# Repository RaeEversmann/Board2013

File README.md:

Board2013
=========

Uses the TI Evaluation boards and breaks out pins plus motor controllers and power regulator to use on various robotic projects. Uses Motor Controller TLE 5205-2G and Buck Regulator LM25765.

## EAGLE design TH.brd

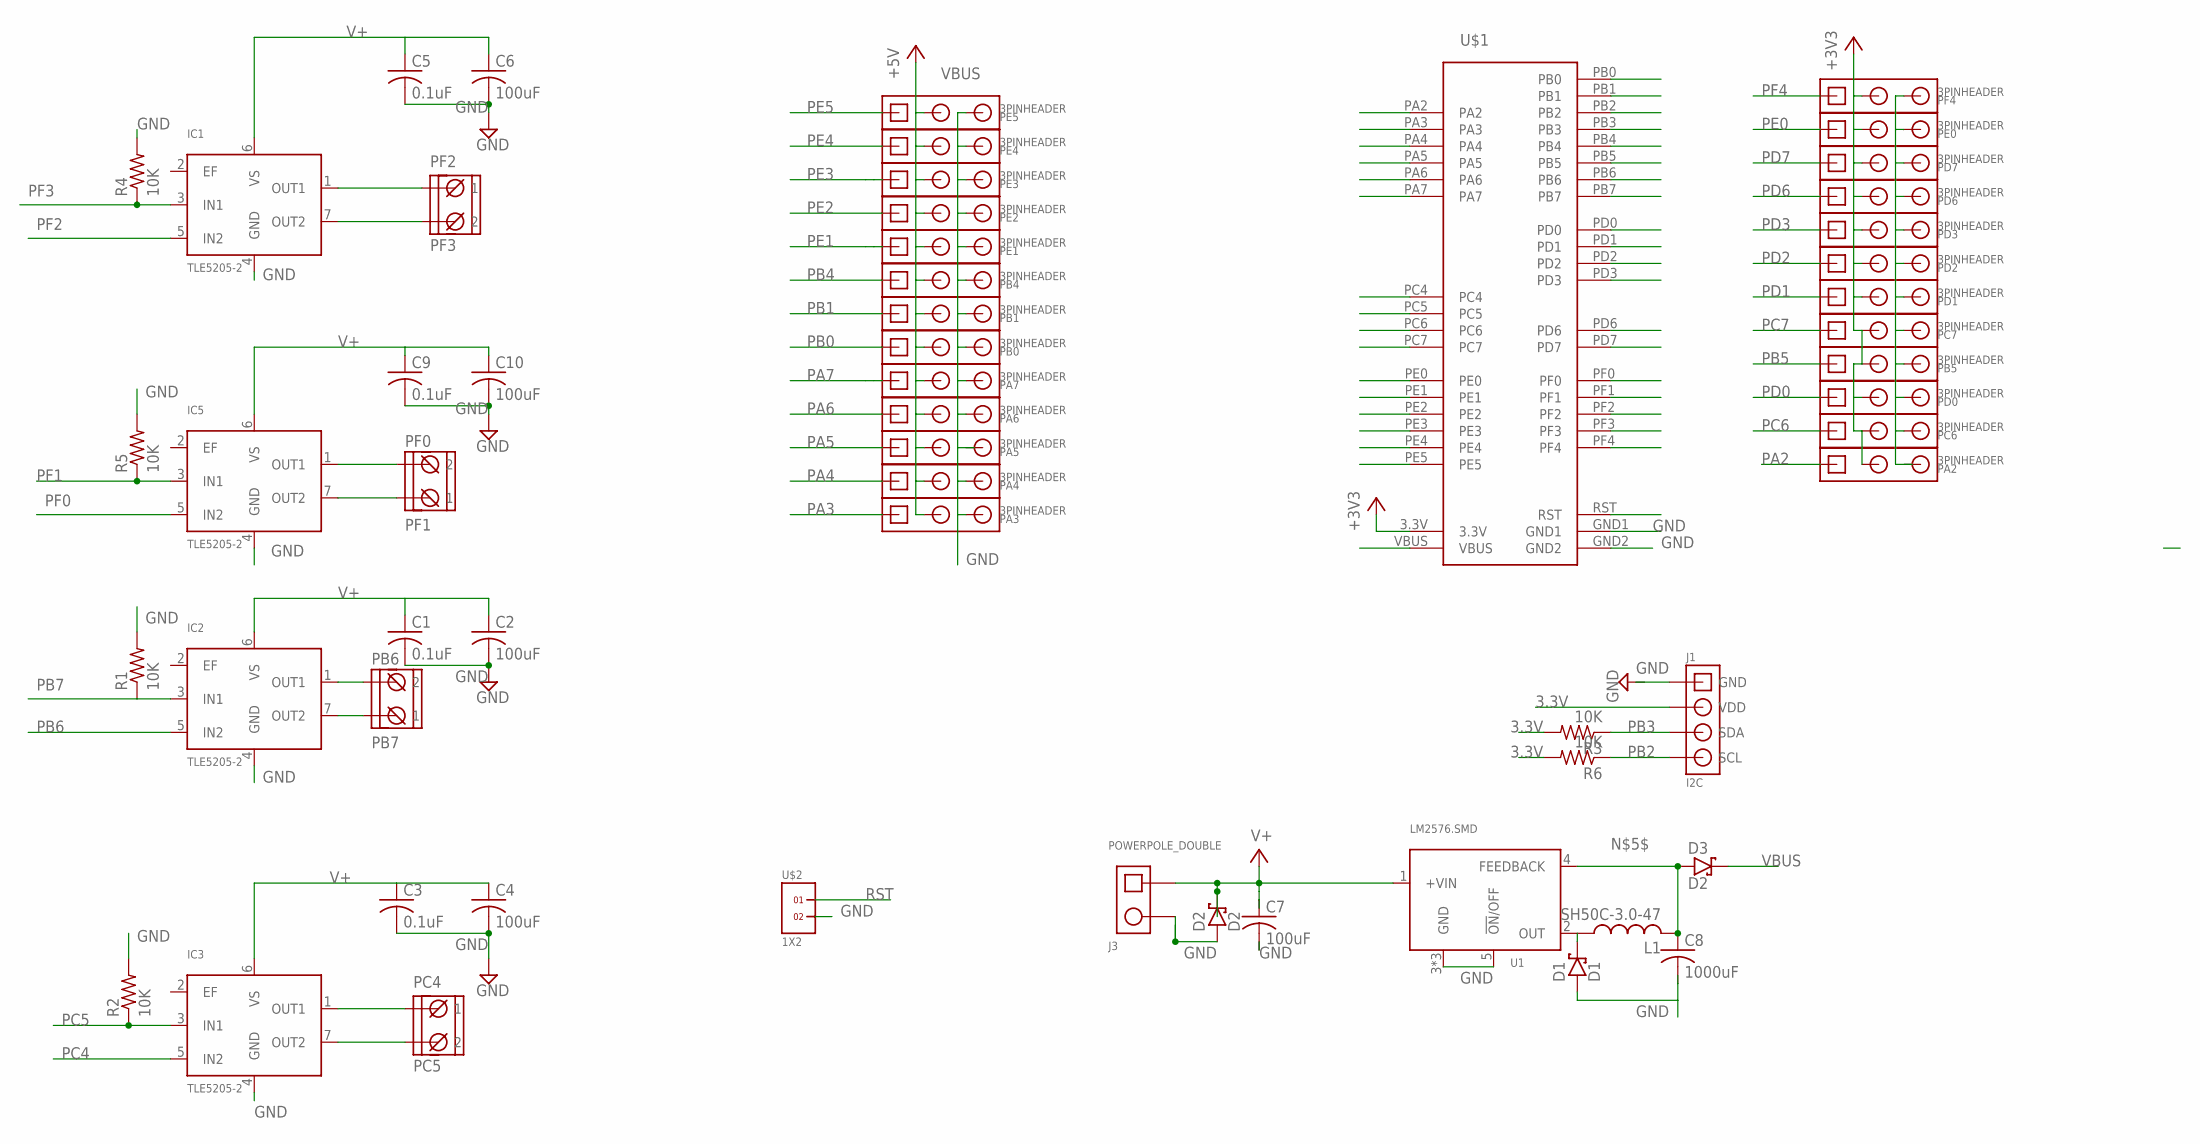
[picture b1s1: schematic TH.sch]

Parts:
C1, C3, C5, C9: 0.1uF; C025-024X044
C2, C4, C6, C10: 100uF; C025-024X044
C7: 100uF; C025-050X050
C8: 1000uF; C025-050X050
D1: D1; DIODE_17MM
D2, D3: D2; DIODE_17MM
IC1, IC2, IC3, IC5: TLE5205-2; TO-220-7-11
J1: I2C; 0.1IN_HEADER_1X4
J3: POWERPOLE_DOUBLE
L1: SH50C-3.0-47; SH50-C2
PA2, PA3, PA4, PA5, PA6, PA7: 3PINHEADER
PB0, PB1, PB4, PB5: 3PINHEADER
PB7: PB6; PHOENIXSCREWTERMINAL_2
PC4: PC5; PHOENIXSCREWTERMINAL_2
PC6, PC7: 3PINHEADER
PD0, PD1, PD2, PD3, PD6, PD7: 3PINHEADER
PE0, PE1, PE2, PE3, PE4, PE5: 3PINHEADER
PF1: PF0; PHOENIXSCREWTERMINAL_2
PF2: PF3; PHOENIXSCREWTERMINAL_2
PF4: 3PINHEADER
R1, R2, R3, R4, R5, R6: 10K; 0204/7
U1: LM2576.SMD; KTT0005B
U$1: STELLARIS-LAUNCHPADSTELLARIS-LAUNCHPAD-XL; LAUNCHPAD-XL
U$2: 1X2

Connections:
3.3V: J1.2 (VDD), PA2.2, PB5.2, PC6.2, PC7.2, PD0.2, PD1.2, PD2.2, PD3.2, PD6.2, PD7.2, PE0.2, PF4.2, R3.2, R6.2, U$1.3.3V
GND: C1.2, C2.2, C3.2, C4.2, C5.2, C6.2, C7.2, C8.2, C9.2, C10.2, D1.2 (A), D2.2 (A), IC1.4 (GND), IC2.4 (GND), IC3.4 (GND), IC5.4 (GND), J1.1 (GND), J3.2, PA3.3, PA4.3, PA5.3, PA6.3, PA7.3, PB0.3, PB1.3, PB4.3, PB5.3, PC6.3, PC7.3, PD0.3, PD1.3, PD2.3, PD3.3, PD6.3, PD7.3, PE0.3, PE1.3, PE2.3, PE3.3, PE4.3, PE5.3, PF4.3, R1.2, R2.2, R4.2, R5.2, U1.3 (GND), U1.5 (!ON!/OFF), U1.GROUND (GND), U1.GROUND@1 (GND), U$1.GND1, U$1.GND2, U$2.2
unnamed: IC2.1 (OUT1), PB7.2
unnamed: IC2.7 (OUT2), PB7.1
unnamed: C8.1, D3.2 (A), L1.P$2 (2), U1.4 (FEEDBACK)
unnamed: IC3.1 (OUT1), PC4.1
unnamed: IC1.1 (OUT1), PF2.1
unnamed: IC1.7 (OUT2), PF2.2
unnamed: IC3.7 (OUT2), PC4.2
unnamed: D1.1 (C), L1.P$1 (1), U1.2 (OUT)
unnamed: IC5.1 (OUT1), PF1.2
unnamed: IC5.7 (OUT2), PF1.1
PA2: PA2.1, U$1.PA2
PA3: PA3.1, U$1.PA3
PA4: PA4.1, U$1.PA4
PA5: PA5.1, U$1.PA5
PA6: PA6.1, U$1.PA6
PA7: PA7.1, U$1.PA7
PB0: PB0.1, U$1.PB0
PB1: PB1.1, U$1.PB1
PB2: J1.4 (SCL), R6.1, U$1.PB2
PB3: J1.3 (SDA), R3.1, U$1.PB3
PB4: PB4.1, U$1.PB4
PB5: PB5.1, U$1.PB5
PB6: IC2.5 (IN2), U$1.PB6
PB7: IC2.3 (IN1), R1.1, U$1.PB7
PC4: IC3.5 (IN2), U$1.PC4
PC5: IC3.3 (IN1), R2.1, U$1.PC5
PC6: PC6.1, U$1.PC6
PC7: PC7.1, U$1.PC7
PD0: PD0.1, U$1.PD0
PD1: PD1.1, U$1.PD1
PD2: PD2.1, U$1.PD2
PD3: PD3.1, U$1.PD3
PD6: PD6.1, U$1.PD6
PD7: PD7.1, U$1.PD7
PE0: PE0.1, U$1.PE0
PE1: PE1.1, U$1.PE1
PE2: PE2.1, U$1.PE2
PE3: PE3.1, U$1.PE3
PE4: PE4.1, U$1.PE4
PE5: PE5.1, U$1.PE5
PF0: IC5.5 (IN2), U$1.PF0
PF1: IC5.3 (IN1), R5.1, U$1.PF1
PF2: IC1.5 (IN2), U$1.PF2
PF3: IC1.3 (IN1), R4.1, U$1.PF3
PF4: PF4.1, U$1.PF4
RST: U$1.RST, U$2.1
V+: C1.1, C2.1, C3.1, C4.1, C5.1, C6.1, C7.1, C9.1, C10.1, D2.1 (C), IC1.6 (VS), IC2.6 (VS), IC3.6 (VS), IC5.6 (VS), J3.1, U1.1 (+VIN)
VBUS: D3.1 (C), PA3.2, PA4.2, PA5.2, PA6.2, PA7.2, PB0.2, PB1.2, PB4.2, PE1.2, PE2.2, PE3.2, PE4.2, PE5.2, U$1.VBUS

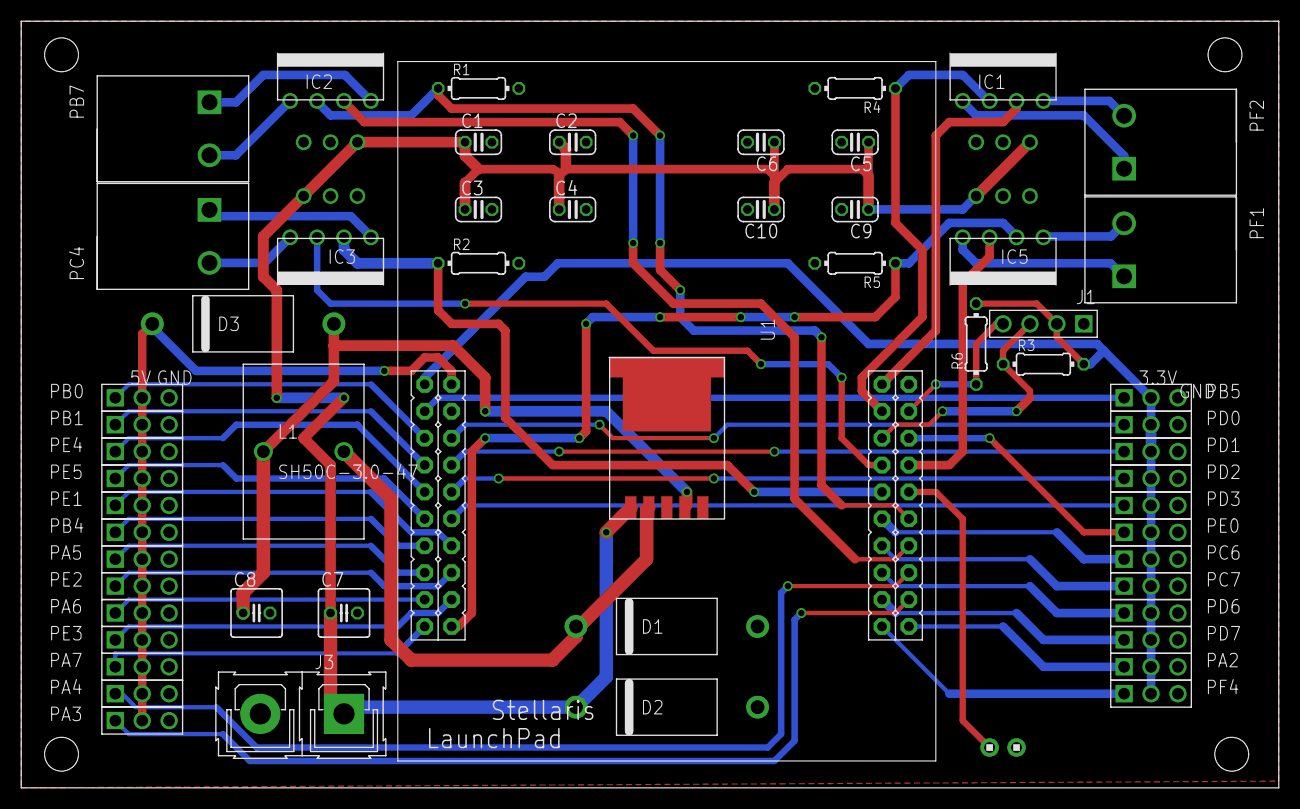
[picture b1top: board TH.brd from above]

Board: 2 copper layers, 118.7 x 72.4 mm, 58 parts (0 on the bottom side), 50 nets.

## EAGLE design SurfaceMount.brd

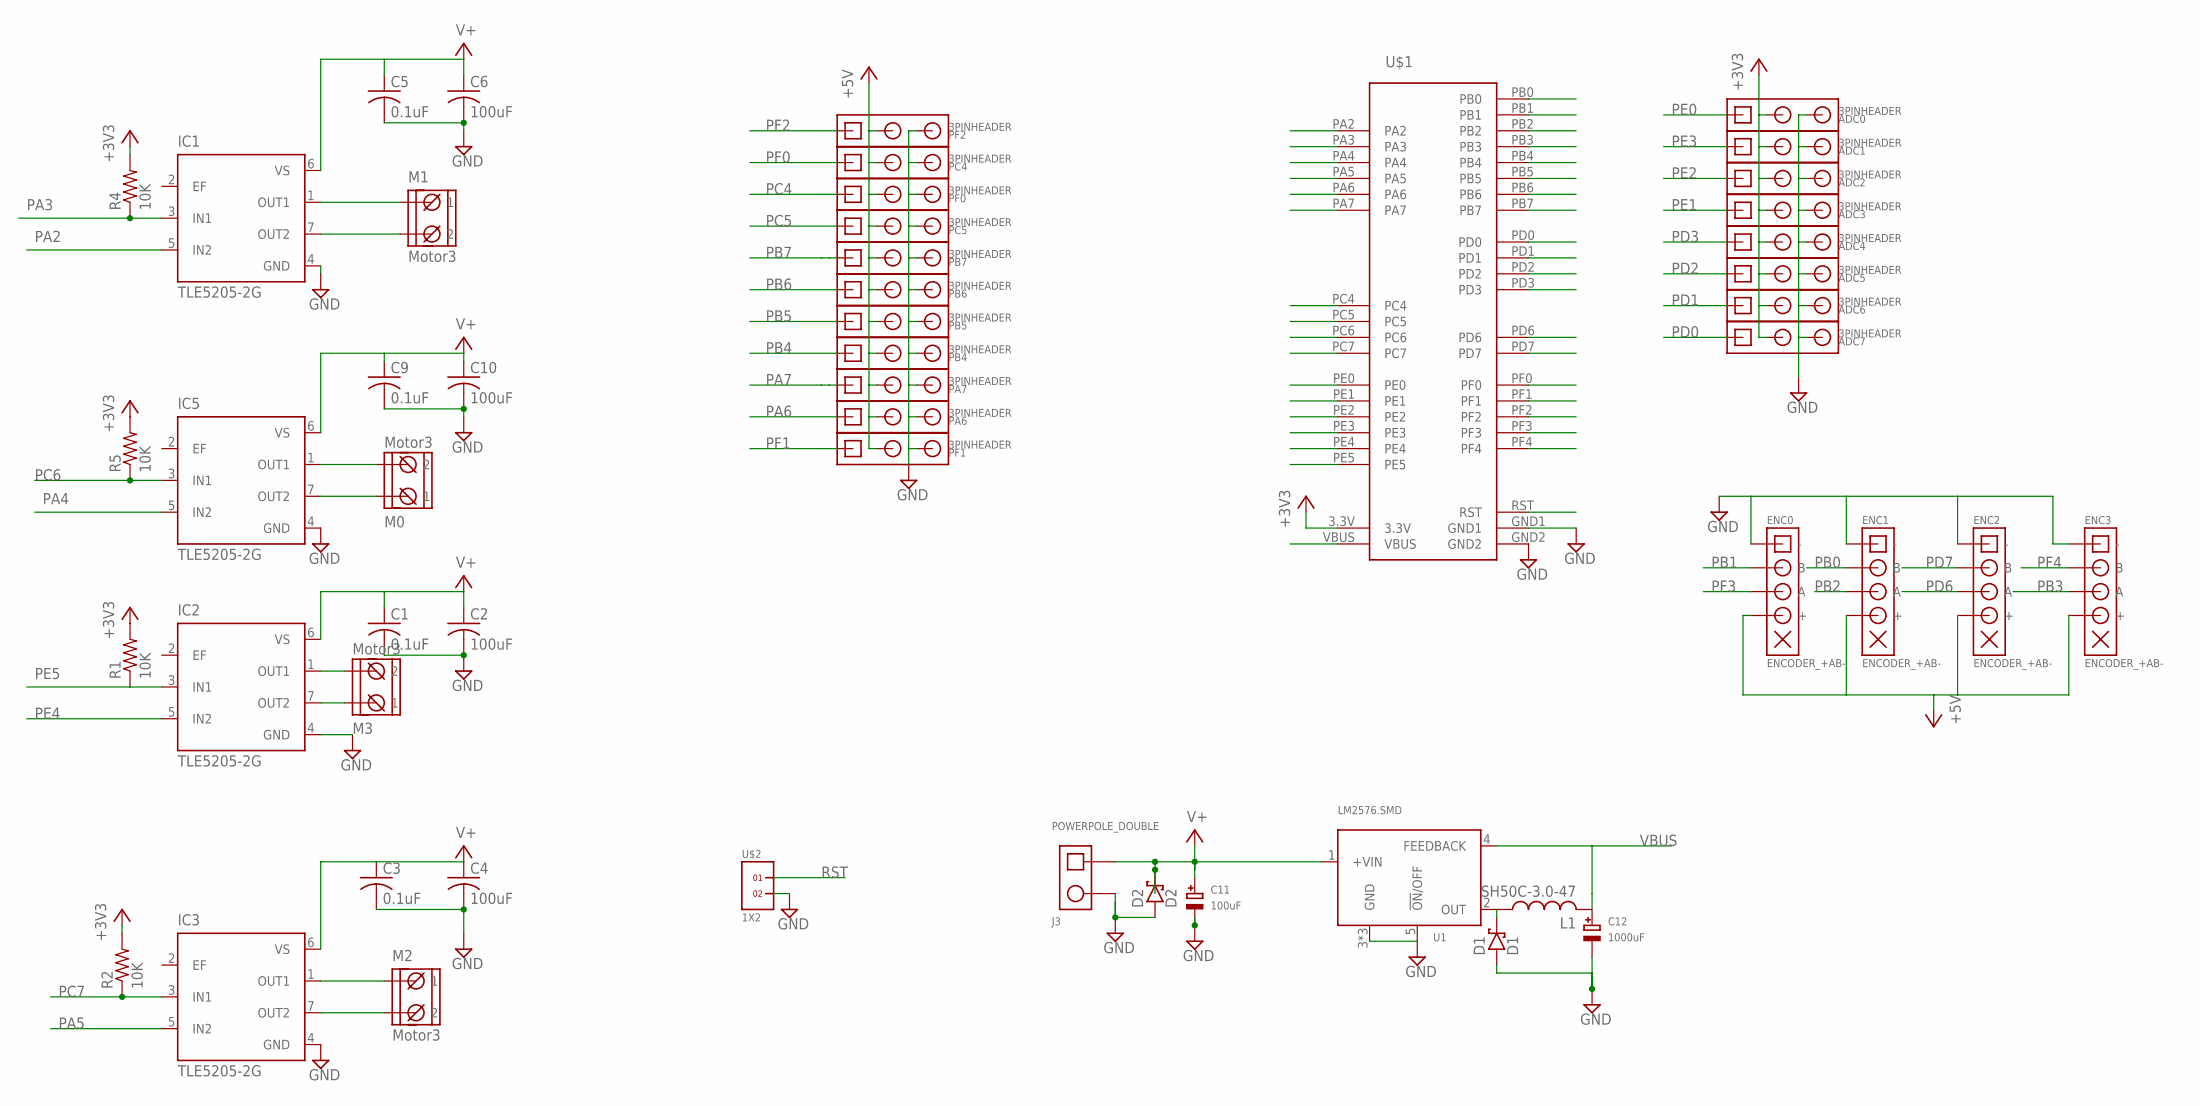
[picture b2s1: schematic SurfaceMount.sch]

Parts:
ADC0, ADC1, ADC2, ADC3, ADC4, ADC5, ADC6, ADC7: 3PINHEADER
C1, C3, C5, C9: 0.1uF; C0603
C2, C4, C6, C10: 100uF; C0603
C11: 100uF; PANASONIC_D
C12: 1000uF; PANASONIC_D
D1: D1; DIODE_17MM
D2: D2; DIODE_17MM
ENC0, ENC1, ENC2, ENC3: ENCODER_+AB-; 0.1IN_HEADER_1X5
IC1, IC2, IC3, IC5: TLE5205-2G; P-TO263-7-1
J3: POWERPOLE_DOUBLE
L1: SH50C-3.0-47; SH50-C2
M0, M1, M2, M3: Motor3; PHOENIXSCREWTERMINAL_2
PA6, PA7: 3PINHEADER
PB4, PB5, PB6, PB7: 3PINHEADER
PC4, PC5: 3PINHEADER
PF0, PF1, PF2: 3PINHEADER
R1, R2, R4, R5: 10K; R0603
U1: LM2576.SMD; KTT0005B
U$1: STELLARIS-LAUNCHPADSTELLARIS-LAUNCHPAD-XL; LAUNCHPAD-XL
U$2: 1X2

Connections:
+3V3: ADC0.2, ADC1.2, ADC2.2, ADC3.2, ADC4.2, ADC5.2, ADC6.2, ADC7.2, R1.2, R2.2, R4.2, R5.2, U$1.3.3V
-GND: ADC0.3, ADC1.3, ADC2.3, ADC3.3, ADC4.3, ADC5.3, ADC6.3, ADC7.3, C1.2, C2.2, C3.2, C4.2, C5.2, C6.2, C9.2, C10.2, C11.-, C12.-, D1.2 (A), D2.2 (A), ENC0.1 (-), ENC1.1 (-), ENC2.1 (-), ENC3.1 (-), IC1.4 (GND), IC2.4 (GND), IC3.4 (GND), IC5.4 (GND), J3.2, PA6.3, PA7.3, PB4.3, PB5.3, PB6.3, PB7.3, PC4.3, PC5.3, PF0.3, PF1.3, PF2.3, U1.3 (GND), U1.5 (!ON!/OFF), U1.GROUND (GND), U1.GROUND@1 (GND), U$1.GND1, U$1.GND2, U$2.2
unnamed: IC2.1 (OUT1), M3.2
unnamed: IC2.7 (OUT2), M3.1
unnamed: IC3.1 (OUT1), M2.1
unnamed: IC1.1 (OUT1), M1.1
unnamed: IC1.7 (OUT2), M1.2
unnamed: IC3.7 (OUT2), M2.2
unnamed: D1.1 (C), L1.P$1 (1), U1.2 (OUT)
unnamed: IC5.1 (OUT1), M0.2
unnamed: IC5.7 (OUT2), M0.1
PA2: IC1.5 (IN2), U$1.PA2
PA3: IC1.3 (IN1), R4.1, U$1.PA3
PA4: IC5.5 (IN2), U$1.PA4
PA5: IC3.5 (IN2), U$1.PA5
PA6: PA6.1, U$1.PA6
PA7: PA7.1, U$1.PA7
PB0: ENC1.2 (B), U$1.PB0
PB1: ENC0.2 (B), U$1.PB1
PB2: ENC1.3 (A), U$1.PB2
PB3: ENC3.3 (A), U$1.PB3
PB4: PB4.1, U$1.PB4
PB5: PB5.1, U$1.PB5
PB6: PB6.1, U$1.PB6
PB7: PB7.1, U$1.PB7
PC4: PF0.1, U$1.PC4
PC5: PC5.1, U$1.PC5
PC6: IC5.3 (IN1), R5.1, U$1.PC6
PC7: IC3.3 (IN1), R2.1, U$1.PC7
PD0: ADC7.1, U$1.PD0
PD1: ADC6.1, U$1.PD1
PD2: ADC5.1, U$1.PD2
PD3: ADC4.1, U$1.PD3
PD6: ENC2.3 (A), U$1.PD6
PD7: ENC2.2 (B), U$1.PD7
PE0: ADC0.1, U$1.PE0
PE1: ADC3.1, U$1.PE1
PE2: ADC2.1, U$1.PE2
PE3: ADC1.1, U$1.PE3
PE4: IC2.5 (IN2), U$1.PE4
PE5: IC2.3 (IN1), R1.1, U$1.PE5
PF0: PC4.1, U$1.PF0
PF1: PF1.1, U$1.PF1
PF2: PF2.1, U$1.PF2
PF3: ENC0.3 (A), U$1.PF3
PF4: ENC3.2 (B), U$1.PF4
RST: U$1.RST, U$2.1
V+: C1.1, C2.1, C3.1, C4.1, C5.1, C6.1, C9.1, C10.1, C11.+, D2.1 (C), IC1.6 (VS), IC2.6 (VS), IC3.6 (VS), IC5.6 (VS), J3.1, U1.1 (+VIN)
VBUS: C12.+, ENC0.4 (+), ENC1.4 (+), ENC2.4 (+), ENC3.4 (+), L1.P$2 (2), PA6.2, PA7.2, PB4.2, PB5.2, PB6.2, PB7.2, PC4.2, PC5.2, PF0.2, PF1.2, PF2.2, U1.4 (FEEDBACK), U$1.VBUS

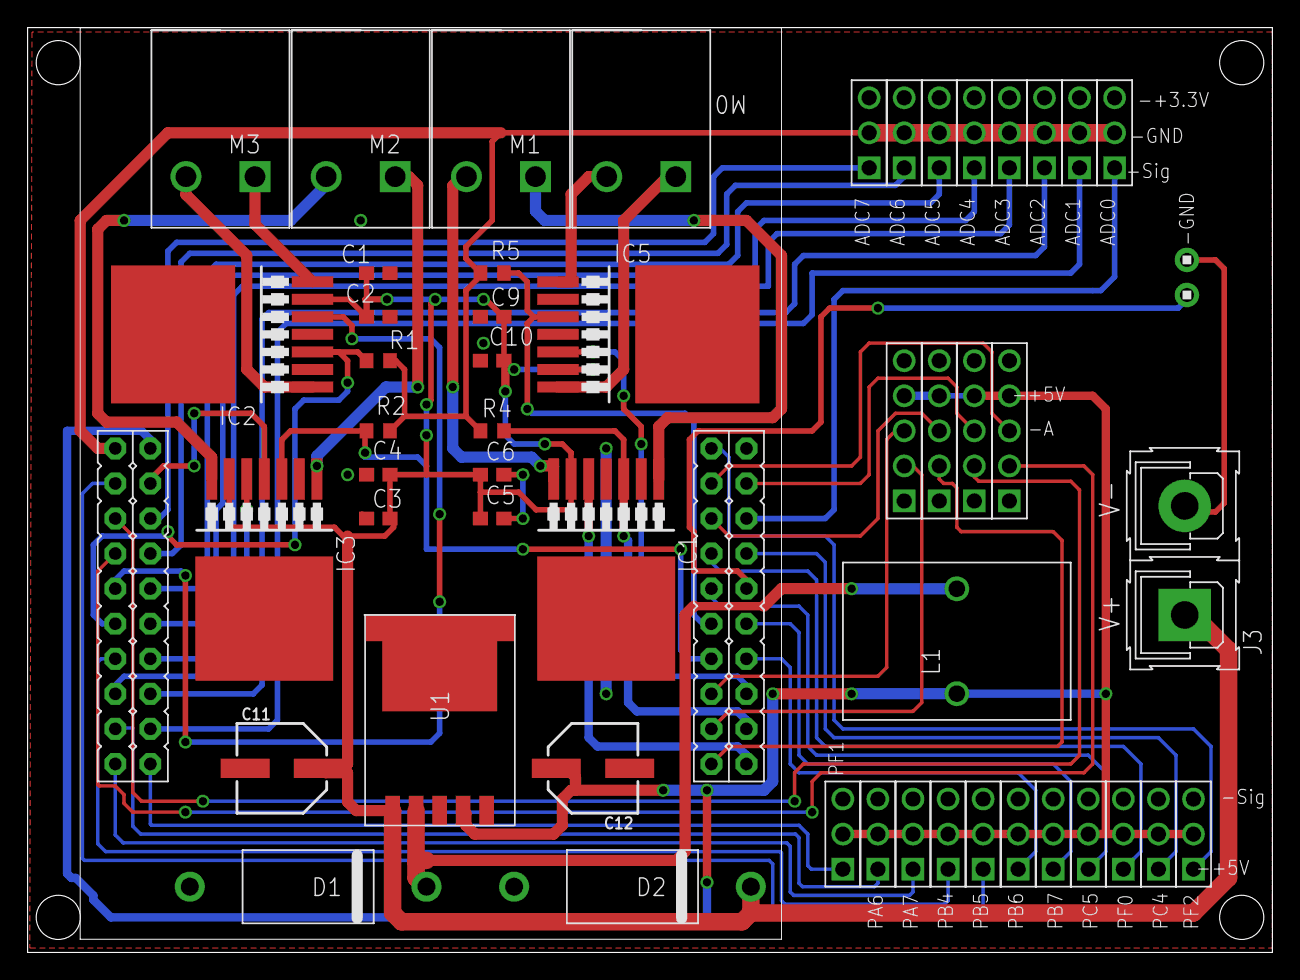
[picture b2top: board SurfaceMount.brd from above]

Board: 2 copper layers, 90.2 x 67.0 mm, 52 parts (0 on the bottom side), 49 nets.

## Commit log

2013-04-29 Added Board Files
2013-05-02 Fixed a few airwires. Removed .b# files (Eagle autogenerated backups) Added .gitignore to ignore unnecessary files
2013-05-02 blah
2013-05-02 Removed the uselss Eagle backup files. Added a .gitingore file to ignore thos files from now on...
2013-05-03 Fixed angle errors
2013-05-03 Cleaned up airwires Added second ground plane Things missing: Silkscreen comments Mounting holes Dounbhe check motor controller IC's pad connections
2013-06-28 changed Readme
2013-07-23 Changed traces slightly
2013-07-25 Made new file for Through hole
    Changed all components to through hole expect power regulator because
    eagle won't let me make a bigger board in the free version
2013-07-26 Finished Traces
    Only thing left to do is label everything, and ground layer, with do
    this tomorrow after TRR
2014-01-16 Final Design

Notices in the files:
parts and their libraries:
microbuilder: This work is placed in the public domain, and may be freely used for commercial and non-commercial work with the following conditions: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
